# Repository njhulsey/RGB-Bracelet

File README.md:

# RGB-Bracelet
A wearable, rechargeable, band of 12 Neopixels

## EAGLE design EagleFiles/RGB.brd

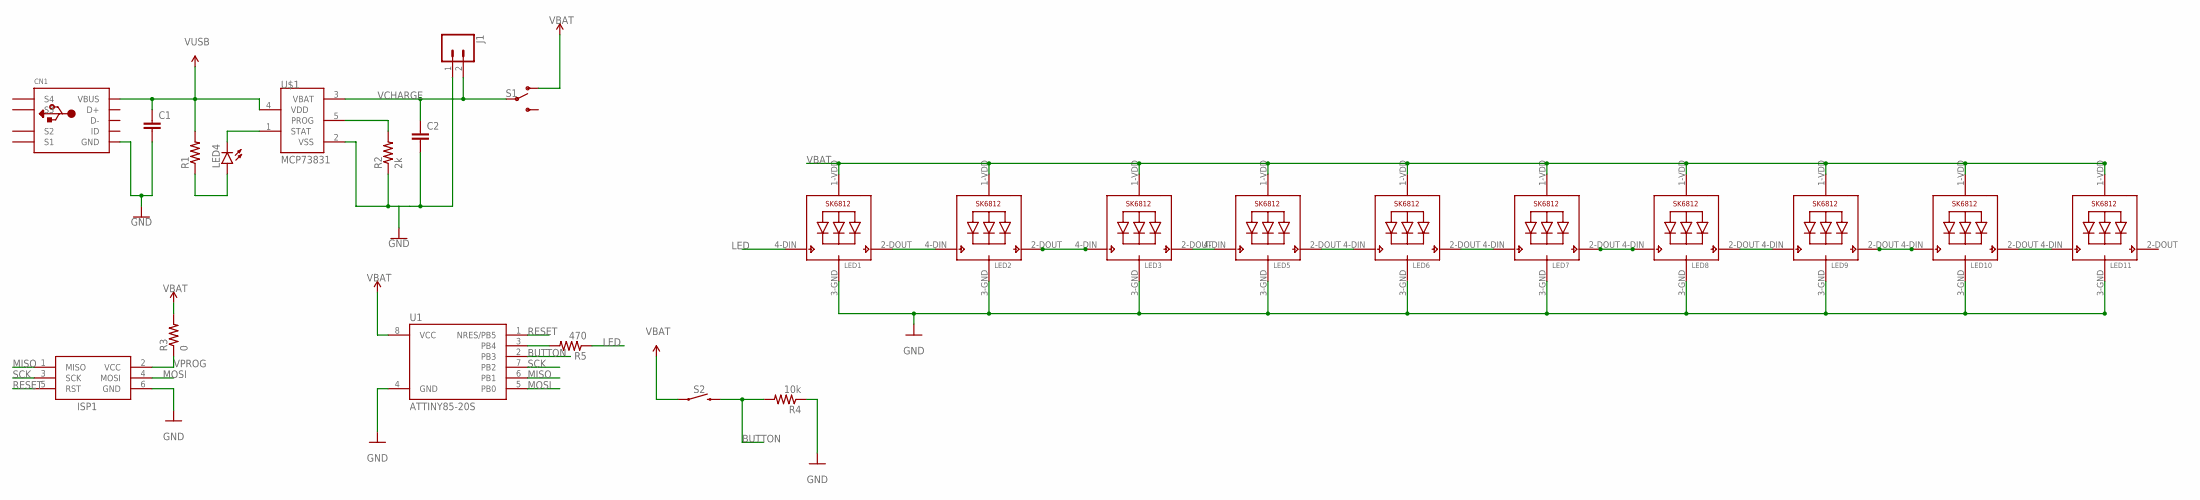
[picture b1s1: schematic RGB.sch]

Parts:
C1, C2: C-EUC0805K; C0805K
CN1: USBMINIB; USB-MINIB
ISP1: AVRISP-6; AVRISP
J1: CONN_02; 1X02
LED1, LED2, LED3, LED5, LED6, LED7, LED8, LED9, LED10, LED11: SK6812_5050W; LED5050_W
LED4: LEDCHIP-LED0805; CHIP-LED0805
R1: R-US_R0805; R0805
R2: 2k; R0805
R3: 0; R0805
R4: 10k; R0805
R5: 470; R0805
S1: SWITCH-SPDT-SMD-RIGHT-ANGLE; SWITCH_SPST_SMD_A
S2: MOMENTARY-SWITCH-SPST-SMD-5.2MM; TACTILE_SWITCH_SMD_5.2MM
U1: ATTINY85-20S; SOIC8_EIAJ_208MIL
U$1: MCP73831; SOT23-5L

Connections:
BUTTON: R4.2, S2.3 (2), U1.2 (PB3)
GND: C1.2, C2.2, CN1.GND, ISP1.6 (GND), J1.1, LED1.3-GND (GND), LED2.3-GND (GND), LED3.3-GND (GND), LED5.3-GND (GND), LED6.3-GND (GND), LED7.3-GND (GND), LED8.3-GND (GND), LED9.3-GND (GND), LED10.3-GND (GND), LED11.3-GND (GND), R2.1, R4.1, U1.4 (GND), U$1.2 (VSS)
LED: LED1.4-DIN (DI), R5.1
MISO: ISP1.1 (MISO), U1.6 (PB1)
MOSI: ISP1.4 (MOSI), U1.5 (PB0)
unnamed: R2.2, U$1.5 (PROG)
unnamed: LED4.C, U$1.1 (STAT)
unnamed: LED4.A, R1.1
unnamed: R5.2, U1.3 (PB4)
unnamed: LED1.2-DOUT (DO), LED2.4-DIN (DI)
unnamed: LED2.2-DOUT (DO), LED3.4-DIN (DI)
unnamed: LED3.2-DOUT (DO), LED5.4-DIN (DI)
unnamed: LED5.2-DOUT (DO), LED6.4-DIN (DI)
unnamed: LED6.2-DOUT (DO), LED7.4-DIN (DI)
unnamed: LED7.2-DOUT (DO), LED8.4-DIN (DI)
unnamed: LED8.2-DOUT (DO), LED9.4-DIN (DI)
unnamed: LED9.2-DOUT (DO), LED10.4-DIN (DI)
unnamed: LED10.2-DOUT (DO), LED11.4-DIN (DI)
RESET: ISP1.5 (RST), U1.1 (NRES/PB5)
SCK: ISP1.3 (SCK), U1.7 (PB2)
VBAT: LED1.1-VDD (VDD), LED2.1-VDD (VDD), LED3.1-VDD (VDD), LED5.1-VDD (VDD), LED6.1-VDD (VDD), LED7.1-VDD (VDD), LED8.1-VDD (VDD), LED9.1-VDD (VDD), LED10.1-VDD (VDD), LED11.1-VDD (VDD), R3.2, S1.1 (O), S2.1, U1.8 (VCC)
VCHARGE: C2.1, J1.2, S1.2, U$1.3 (VBAT)
VPROG: ISP1.2 (VCC), R3.1
VUSB: C1.1, CN1.VBUS, R1.2, U$1.4 (VDD)

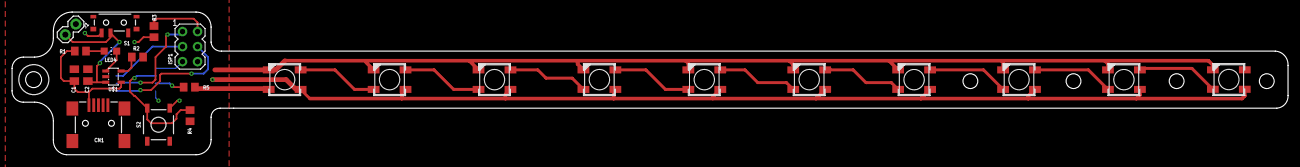
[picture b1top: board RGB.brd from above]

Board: 2 copper layers, 215.8 x 24.1 mm, 25 parts (1 on the bottom side), 24 nets.

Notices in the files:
parts and their libraries:
microbuilder: This work is placed in the public domain, and may be freely used for commercial and non-commercial work with the following conditions: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
SparkFun-Connectors: Licensing: Creative Commons ShareAlike 4.0 International - https://creativecommons.org/licenses/by-sa/4.0
